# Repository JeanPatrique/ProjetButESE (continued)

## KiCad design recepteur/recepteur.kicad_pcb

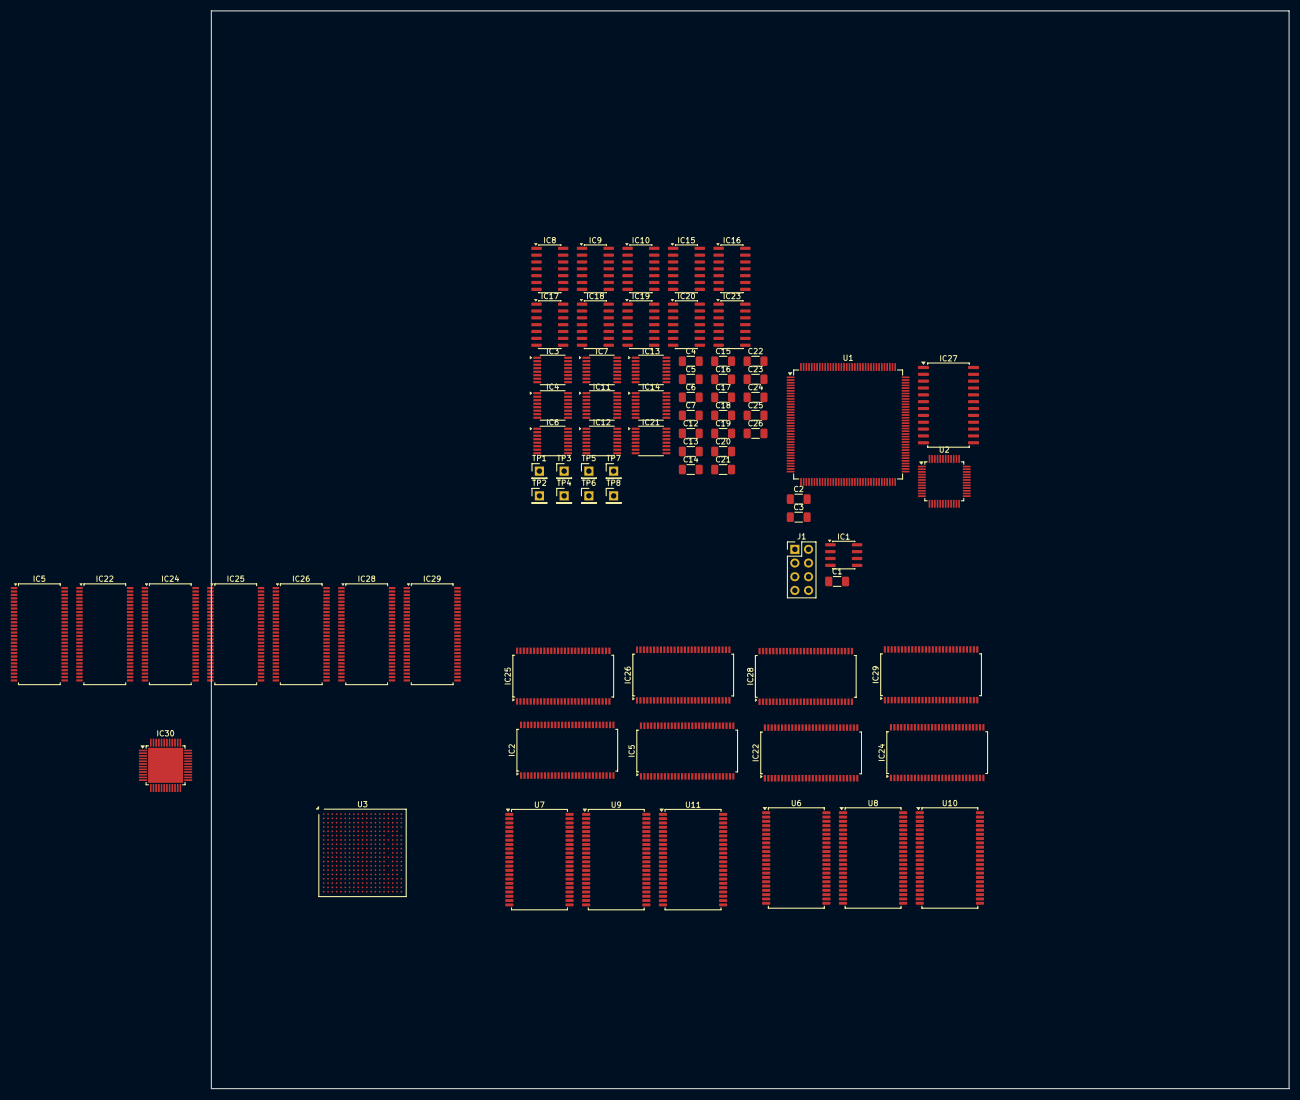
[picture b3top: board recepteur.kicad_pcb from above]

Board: 2 copper layers, 200.0 x 200.0 mm, 77 parts (0 on the bottom side), 311 nets.

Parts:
C1, C2, C3: C; C_1206_3216Metric_Pad1.33x1.80mm_HandSolder
C4, C5, C6, C7, C12, C13, C14, C15, C16, C17, C18, C19, C20, C21, C22, C23, C24, C25, C26: 100nF; C_1206_3216Metric_Pad1.33x1.80mm_HandSolder
IC1: 551MLF; SOIC-8_3.9x4.9mm_P1.27mm
IC2, IC5, IC5#2, IC22, IC22#2, IC24, IC24#2, IC25, IC25#2, IC26, IC26#2, IC28, IC28#2, IC29, IC29#2: SN74CBTD16211DLR; SSOP-56_7.5x18.5mm_P0.635mm
IC3, IC4, IC6, IC7: SN74LV4040APWR; TSSOP-16_4.4x5mm_P0.65mm
IC8, IC9, IC10, IC15, IC16, IC17, IC18, IC19, IC20, IC23: SN74F21DRE4; SOIC-14_3.9x8.7mm_P1.27mm
IC11, IC12, IC13, IC14, IC21: 74VHC112; TSSOP-16_4.4x5mm_P0.65mm
IC27: SN74LVCC4245A; SOIC-24W_7.5x15.4mm_P1.27mm
IC30: THS8135PHP; Texas_PHP0048E_HTQFP-48-1EP_7x7mm_P0.5mm_EP6.5x6.5mm_Mask3.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
J1: Conn_02x04_Counter_Clockwise; PinHeader_2x04_P2.54mm_Vertical
TP1, TP2, TP3, TP4, TP5, TP6, TP7, TP8: TestPoint; PinHeader_1x01_P2.54mm_Vertical
U1: STM32H733ZGTx; LQFP-144_20x20mm_P0.5mm
U2: STM32H523CETx; LQFP-48_7x7mm_P0.5mm
U3: STM32MP151DABx; ST_LFBGA-354_16x16mm_Layout19x19_P0.8mm
U6, U7, U8, U9, U10, U11: IS61C5128AL-10TLI; TSOP-II-44_10.16x18.41mm_P0.8mm

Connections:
/MCU/40MHZ_pixel_clock: IC1.1 (ICLK), IC27.3 (A0), IC27.21 (B0)
/MCU/RESET: IC27.5 (A2), IC27.19 (B2)
/MCU/pixelBufferMemoryAddress.A_{0}: IC24#2.54 (B_{1}_1), IC28#2.54 (B_{1}_1)
/MCU/pixelBufferMemoryAddress.A_{1}: IC24#2.53 (B_{1}_2), IC28#2.53 (B_{1}_2)
/MCU/pixelBufferMemoryAddress.A_{2}: IC24#2.52 (B_{1}_3), IC28#2.52 (B_{1}_3)
/MCU/pixelBufferMemoryAddress.A_{3}: IC24#2.51 (B_{1}_4), IC28#2.51 (B_{1}_4)
/MCU/pixelBufferMemoryAddress.A_{4}: IC24#2.50 (B_{1}_5), IC28#2.50 (B_{1}_5)
/MCU/pixelBufferMemoryAddress.A_{5}: IC24#2.48 (B_{1}_6), IC28#2.48 (B_{1}_6)
/MCU/pixelBufferMemoryAddress.A_{6}: IC24#2.47 (B_{1}_7), IC28#2.47 (B_{1}_7)
/MCU/pixelBufferMemoryAddress.A_{7}: IC24#2.46 (B_{1}_8), IC28#2.46 (B_{1}_8)
/MCU/pixelBufferMemoryAddress.A_{8}: IC24#2.45 (B_{1}_9), IC28#2.45 (B_{1}_9)
/MCU/pixelBufferMemoryAddress.A_{9}: IC24#2.44 (B_{1}_10), IC28#2.44 (B_{1}_10)
/MCU/pixelBufferMemoryAddress.A_{10}: IC24#2.43 (B_{1}_11), IC28#2.43 (B_{1}_11)
/MCU/pixelBufferMemoryAddress.A_{11}: IC24#2.42 (B_{1}_12), IC28#2.42 (B_{1}_12)
/MCU/pixelBufferMemoryAddress.A_{12}: IC24#2.41 (B_{2}_1), IC28#2.41 (B_{2}_1)
/MCU/pixelBufferMemoryAddress.A_{13}: IC24#2.40 (B_{2}_2), IC28#2.40 (B_{2}_2)
/MCU/pixelBufferMemoryAddress.A_{14}: IC24#2.39 (B_{2}_3), IC28#2.39 (B_{2}_3)
/MCU/pixelBufferMemoryAddress.A_{15}: IC24#2.37 (B_{2}_4), IC28#2.37 (B_{2}_4)
/MCU/pixelBufferMemoryAddress.A_{16}: IC24#2.36 (B_{2}_5), IC28#2.36 (B_{2}_5)
/MCU/pixelBufferMemoryAddress.A_{17}: IC24#2.35 (B_{2}_6), IC28#2.35 (B_{2}_6)
/MCU/pixelBufferMemoryAddress.A_{18}: IC24#2.34 (B_{2}_7), IC28#2.34 (B_{2}_7)
/MCU/pixelBuffer~WE: IC5.33 (B_{2}_8), IC24.33 (B_{2}_8), IC24#2.33 (B_{2}_8), IC28#2.33 (B_{2}_8)
/MCU/videoBufferSwapRequest_5V: IC19.8 (&), IC23.4 (C), IC23.5 (D), TP3.1
/MCU/~MCU_ACK_bufferSwap: IC23.1 (A), IC23.2 (B), IC27.10 (A7), IC27.14 (B7)
/Memory_bank_{0}/address.A_{0}: IC22.2 (A_{1}_1), IC24#2.2 (A_{1}_1)
/Memory_bank_{0}/address.A_{1}: IC22.3 (A_{1}_2), IC24#2.3 (A_{1}_2)
/Memory_bank_{0}/address.A_{2}: IC22.4 (A_{1}_3), IC24#2.4 (A_{1}_3)
/Memory_bank_{0}/address.A_{3}: IC22.5 (A_{1}_4), IC24#2.5 (A_{1}_4)
/Memory_bank_{0}/address.A_{4}: IC22.6 (A_{1}_5), IC24#2.6 (A_{1}_5)
/Memory_bank_{0}/address.A_{5}: IC22.7 (A_{1}_6), IC24#2.7 (A_{1}_6)
/Memory_bank_{0}/address.A_{6}: IC22.9 (A_{1}_7), IC24#2.9 (A_{1}_7)
/Memory_bank_{0}/address.A_{7}: IC22.10 (A_{1}_8), IC24#2.10 (A_{1}_8)
/Memory_bank_{0}/address.A_{8}: IC22.11 (A_{1}_9), IC24#2.11 (A_{1}_9)
/Memory_bank_{0}/address.A_{9}: IC22.12 (A_{1}_10), IC24#2.12 (A_{1}_10)
/Memory_bank_{0}/address.A_{10}: IC22.13 (A_{1}_11), IC24#2.13 (A_{1}_11)
/Memory_bank_{0}/address.A_{11}: IC22.14 (A_{1}_12), IC24#2.14 (A_{1}_12)
/Memory_bank_{0}/address.A_{12}: IC22.15 (A_{2}_1), IC24#2.15 (A_{2}_1)
/Memory_bank_{0}/address.A_{13}: IC22.16 (A_{2}_2), IC24#2.16 (A_{2}_2)
/Memory_bank_{0}/address.A_{14}: IC22.18 (A_{2}_3), IC24#2.18 (A_{2}_3)
/Memory_bank_{0}/address.A_{15}: IC22.20 (A_{2}_4), IC24#2.20 (A_{2}_4)
/Memory_bank_{0}/address.A_{16}: IC22.21 (A_{2}_5), IC24#2.21 (A_{2}_5)
/Memory_bank_{0}/address.A_{17}: IC22.22 (A_{2}_6), IC24#2.22 (A_{2}_6)
/Memory_bank_{0}/address.A_{18}: IC22.23 (A_{2}_7), IC24#2.23 (A_{2}_7)
/Memory_bank_{0}/data.D_{0}: IC2.2 (A_{1}_1), IC5#2.2 (A_{1}_1), U6.9 (I/O0)
/Memory_bank_{0}/data.D_{1}: IC2.3 (A_{1}_2), IC5#2.3 (A_{1}_2), U6.10 (I/O1)
/Memory_bank_{0}/data.D_{2}: IC2.4 (A_{1}_3), IC5#2.4 (A_{1}_3), U6.13 (I/O2)
/Memory_bank_{0}/data.D_{3}: IC2.5 (A_{1}_4), IC5#2.5 (A_{1}_4), U6.14 (I/O3)
/Memory_bank_{0}/data.D_{4}: IC2.6 (A_{1}_5), IC5#2.6 (A_{1}_5), U6.31 (I/O4)
/Memory_bank_{0}/data.D_{5}: IC2.7 (A_{1}_6), IC5#2.7 (A_{1}_6), U6.32 (I/O5)
/Memory_bank_{0}/data.D_{6}: IC2.9 (A_{1}_7), IC5#2.9 (A_{1}_7), U6.35 (I/O6)
/Memory_bank_{0}/data.D_{7}: IC2.10 (A_{1}_8), IC5#2.10 (A_{1}_8), U6.36 (I/O7)
/Memory_bank_{0}/data.D_{8}: IC2.11 (A_{1}_9), IC5#2.11 (A_{1}_9), U8.9 (I/O0)
/Memory_bank_{0}/data.D_{9}: IC2.12 (A_{1}_10), IC5#2.12 (A_{1}_10), U8.10 (I/O1)
/Memory_bank_{0}/data.D_{10}: IC2.13 (A_{1}_11), IC5#2.13 (A_{1}_11), U8.13 (I/O2)
/Memory_bank_{0}/data.D_{11}: IC2.14 (A_{1}_12), IC5#2.14 (A_{1}_12), U8.14 (I/O3)
/Memory_bank_{0}/data.D_{12}: IC2.15 (A_{2}_1), IC5#2.15 (A_{2}_1), U8.31 (I/O4)
/Memory_bank_{0}/data.D_{13}: IC2.16 (A_{2}_2), IC5#2.16 (A_{2}_2), U8.32 (I/O5)
/Memory_bank_{0}/data.D_{14}: IC2.18 (A_{2}_3), IC5#2.18 (A_{2}_3), U8.35 (I/O6)
/Memory_bank_{0}/data.D_{15}: IC2.20 (A_{2}_4), IC5#2.20 (A_{2}_4), U8.36 (I/O7)
/Memory_bank_{0}/data.D_{16}: IC2.21 (A_{2}_5), IC5#2.21 (A_{2}_5), U10.9 (I/O0)
/Memory_bank_{0}/data.D_{17}: IC2.22 (A_{2}_6), IC5#2.22 (A_{2}_6), U10.10 (I/O1)
/Memory_bank_{0}/data.D_{18}: IC2.23 (A_{2}_7), IC5#2.23 (A_{2}_7), U10.13 (I/O2)
/Memory_bank_{0}/data.D_{19}: IC2.24 (A_{2}_8), IC5#2.24 (A_{2}_8), U10.14 (I/O3)
/Memory_bank_{0}/data.D_{20}: IC2.25 (A_{2}_9), IC5#2.25 (A_{2}_9), U10.31 (I/O4)
/Memory_bank_{0}/data.D_{21}: IC2.26 (A_{2}_10), IC5#2.26 (A_{2}_10), U10.32 (I/O5)
/Memory_bank_{0}/data.D_{22}: IC2.27 (A_{2}_11), IC5#2.27 (A_{2}_11), U10.35 (I/O6)
/Memory_bank_{0}/data.D_{23}: IC2.28 (A_{2}_12), IC5#2.28 (A_{2}_12), U10.36 (I/O7)
/Memory_bank_{0}/pixelMemoryAddress.A_{0}: U6.3 (A0), U8.3 (A0), U10.3 (A0)
/Memory_bank_{0}/pixelMemoryAddress.A_{1}: U6.4 (A1), U8.4 (A1), U10.4 (A1)
/Memory_bank_{0}/pixelMemoryAddress.A_{2}: U6.5 (A2), U8.5 (A2), U10.5 (A2)
/Memory_bank_{0}/pixelMemoryAddress.A_{3}: U6.6 (A3), U8.6 (A3), U10.6 (A3)
/Memory_bank_{0}/pixelMemoryAddress.A_{4}: U6.7 (A4), U8.7 (A4), U10.7 (A4)
/Memory_bank_{0}/pixelMemoryAddress.A_{5}: U6.16 (A5), U8.16 (A5), U10.16 (A5)
/Memory_bank_{0}/pixelMemoryAddress.A_{6}: U6.17 (A6), U8.17 (A6), U10.17 (A6)
/Memory_bank_{0}/pixelMemoryAddress.A_{7}: U6.18 (A7), U8.18 (A7), U10.18 (A7)
/Memory_bank_{0}/pixelMemoryAddress.A_{8}: U6.19 (A8), U8.19 (A8), U10.19 (A8)
/Memory_bank_{0}/pixelMemoryAddress.A_{9}: U6.20 (A9), U8.20 (A9), U10.20 (A9)
/Memory_bank_{0}/pixelMemoryAddress.A_{10}: U6.26 (A10), U8.26 (A10), U10.26 (A10)
/Memory_bank_{0}/pixelMemoryAddress.A_{11}: U6.27 (A11), U8.27 (A11), U10.27 (A11)
/Memory_bank_{0}/pixelMemoryAddress.A_{12}: U6.28 (A12), U8.28 (A12), U10.28 (A12)
/Memory_bank_{0}/pixelMemoryAddress.A_{13}: U6.29 (A13), U8.29 (A13), U10.29 (A13)
/Memory_bank_{0}/pixelMemoryAddress.A_{14}: U6.30 (A14), U8.30 (A14), U10.30 (A14)
/Memory_bank_{0}/pixelMemoryAddress.A_{15}: U6.38 (A15), U8.38 (A15), U10.38 (A15)
/Memory_bank_{0}/pixelMemoryAddress.A_{16}: U6.39 (A16), U8.39 (A16), U10.39 (A16)
/Memory_bank_{0}/pixelMemoryAddress.A_{17}: U6.40 (A17), U8.40 (A17), U10.40 (A17)
/Memory_bank_{0}/pixelMemoryAddress.A_{18}: U6.41 (A18), U8.41 (A18), U10.41 (A18)
/Memory_bank_{1}/address.A_{0}: IC28#2.2 (A_{1}_1), IC29#2.2 (A_{1}_1)
/Memory_bank_{1}/address.A_{1}: IC28#2.3 (A_{1}_2), IC29#2.3 (A_{1}_2)
/Memory_bank_{1}/address.A_{2}: IC28#2.4 (A_{1}_3), IC29#2.4 (A_{1}_3)
/Memory_bank_{1}/address.A_{3}: IC28#2.5 (A_{1}_4), IC29#2.5 (A_{1}_4)
/Memory_bank_{1}/address.A_{4}: IC28#2.6 (A_{1}_5), IC29#2.6 (A_{1}_5)
/Memory_bank_{1}/address.A_{5}: IC28#2.7 (A_{1}_6), IC29#2.7 (A_{1}_6)
/Memory_bank_{1}/address.A_{6}: IC28#2.9 (A_{1}_7), IC29#2.9 (A_{1}_7)
/Memory_bank_{1}/address.A_{7}: IC28#2.10 (A_{1}_8), IC29#2.10 (A_{1}_8)
/Memory_bank_{1}/address.A_{8}: IC28#2.11 (A_{1}_9), IC29#2.11 (A_{1}_9)
/Memory_bank_{1}/address.A_{9}: IC28#2.12 (A_{1}_10), IC29#2.12 (A_{1}_10)
/Memory_bank_{1}/address.A_{10}: IC28#2.13 (A_{1}_11), IC29#2.13 (A_{1}_11)
/Memory_bank_{1}/address.A_{11}: IC28#2.14 (A_{1}_12), IC29#2.14 (A_{1}_12)
/Memory_bank_{1}/address.A_{12}: IC28#2.15 (A_{2}_1), IC29#2.15 (A_{2}_1)
/Memory_bank_{1}/address.A_{13}: IC28#2.16 (A_{2}_2), IC29#2.16 (A_{2}_2)
/Memory_bank_{1}/address.A_{14}: IC28#2.18 (A_{2}_3), IC29#2.18 (A_{2}_3)
/Memory_bank_{1}/address.A_{15}: IC28#2.20 (A_{2}_4), IC29#2.20 (A_{2}_4)
/Memory_bank_{1}/address.A_{16}: IC28#2.21 (A_{2}_5), IC29#2.21 (A_{2}_5)
/Memory_bank_{1}/address.A_{17}: IC28#2.22 (A_{2}_6), IC29#2.22 (A_{2}_6)
/Memory_bank_{1}/address.A_{18}: IC28#2.23 (A_{2}_7), IC29#2.23 (A_{2}_7)
/Memory_bank_{1}/data.D_{0}: IC25#2.2 (A_{1}_1), IC26.2 (A_{1}_1), U7.9 (I/O0)
/Memory_bank_{1}/data.D_{1}: IC25#2.3 (A_{1}_2), IC26.3 (A_{1}_2), U7.10 (I/O1)
/Memory_bank_{1}/data.D_{2}: IC25#2.4 (A_{1}_3), IC26.4 (A_{1}_3), U7.13 (I/O2)
/Memory_bank_{1}/data.D_{3}: IC25#2.5 (A_{1}_4), IC26.5 (A_{1}_4), U7.14 (I/O3)
/Memory_bank_{1}/data.D_{4}: IC25#2.6 (A_{1}_5), IC26.6 (A_{1}_5), U7.31 (I/O4)
/Memory_bank_{1}/data.D_{5}: IC25#2.7 (A_{1}_6), IC26.7 (A_{1}_6), U7.32 (I/O5)
/Memory_bank_{1}/data.D_{6}: IC25#2.9 (A_{1}_7), IC26.9 (A_{1}_7), U7.35 (I/O6)
/Memory_bank_{1}/data.D_{7}: IC25#2.10 (A_{1}_8), IC26.10 (A_{1}_8), U7.36 (I/O7)
/Memory_bank_{1}/data.D_{8}: IC25#2.11 (A_{1}_9), IC26.11 (A_{1}_9), U9.9 (I/O0)
/Memory_bank_{1}/data.D_{9}: IC25#2.12 (A_{1}_10), IC26.12 (A_{1}_10), U9.10 (I/O1)
/Memory_bank_{1}/data.D_{10}: IC25#2.13 (A_{1}_11), IC26.13 (A_{1}_11), U9.13 (I/O2)
/Memory_bank_{1}/data.D_{11}: IC25#2.14 (A_{1}_12), IC26.14 (A_{1}_12), U9.14 (I/O3)
/Memory_bank_{1}/data.D_{12}: IC25#2.15 (A_{2}_1), IC26.15 (A_{2}_1), U9.31 (I/O4)
/Memory_bank_{1}/data.D_{13}: IC25#2.16 (A_{2}_2), IC26.16 (A_{2}_2), U9.32 (I/O5)
/Memory_bank_{1}/data.D_{14}: IC25#2.18 (A_{2}_3), IC26.18 (A_{2}_3), U9.35 (I/O6)
/Memory_bank_{1}/data.D_{15}: IC25#2.20 (A_{2}_4), IC26.20 (A_{2}_4), U9.36 (I/O7)
/Memory_bank_{1}/data.D_{16}: IC25#2.21 (A_{2}_5), IC26.21 (A_{2}_5), U11.9 (I/O0)
/Memory_bank_{1}/data.D_{17}: IC25#2.22 (A_{2}_6), IC26.22 (A_{2}_6), U11.10 (I/O1)
/Memory_bank_{1}/data.D_{18}: IC25#2.23 (A_{2}_7), IC26.23 (A_{2}_7), U11.13 (I/O2)
/Memory_bank_{1}/data.D_{19}: IC25#2.24 (A_{2}_8), IC26.24 (A_{2}_8), U11.14 (I/O3)
/Memory_bank_{1}/data.D_{20}: IC25#2.25 (A_{2}_9), IC26.25 (A_{2}_9), U11.31 (I/O4)
/Memory_bank_{1}/data.D_{21}: IC25#2.26 (A_{2}_10), IC26.26 (A_{2}_10), U11.32 (I/O5)
/Memory_bank_{1}/data.D_{22}: IC25#2.27 (A_{2}_11), IC26.27 (A_{2}_11), U11.35 (I/O6)
/Memory_bank_{1}/data.D_{23}: IC25#2.28 (A_{2}_12), IC26.28 (A_{2}_12), U11.36 (I/O7)
/Memory_bank_{1}/pixelMemoryAddress.A_{0}: U7.3 (A0), U9.3 (A0), U11.3 (A0)
/Memory_bank_{1}/pixelMemoryAddress.A_{1}: U7.4 (A1), U9.4 (A1), U11.4 (A1)
/Memory_bank_{1}/pixelMemoryAddress.A_{2}: U7.5 (A2), U9.5 (A2), U11.5 (A2)
/Memory_bank_{1}/pixelMemoryAddress.A_{3}: U7.6 (A3), U9.6 (A3), U11.6 (A3)
/Memory_bank_{1}/pixelMemoryAddress.A_{4}: U7.7 (A4), U9.7 (A4), U11.7 (A4)
/Memory_bank_{1}/pixelMemoryAddress.A_{5}: U7.16 (A5), U9.16 (A5), U11.16 (A5)
/Memory_bank_{1}/pixelMemoryAddress.A_{6}: U7.17 (A6), U9.17 (A6), U11.17 (A6)
/Memory_bank_{1}/pixelMemoryAddress.A_{7}: U7.18 (A7), U9.18 (A7), U11.18 (A7)
/Memory_bank_{1}/pixelMemoryAddress.A_{8}: U7.19 (A8), U9.19 (A8), U11.19 (A8)
/Memory_bank_{1}/pixelMemoryAddress.A_{9}: U7.20 (A9), U9.20 (A9), U11.20 (A9)
/Memory_bank_{1}/pixelMemoryAddress.A_{10}: U7.26 (A10), U9.26 (A10), U11.26 (A10)
/Memory_bank_{1}/pixelMemoryAddress.A_{11}: U7.27 (A11), U9.27 (A11), U11.27 (A11)
/Memory_bank_{1}/pixelMemoryAddress.A_{12}: U7.28 (A12), U9.28 (A12), U11.28 (A12)
/Memory_bank_{1}/pixelMemoryAddress.A_{13}: U7.29 (A13), U9.29 (A13), U11.29 (A13)
/Memory_bank_{1}/pixelMemoryAddress.A_{14}: U7.30 (A14), U9.30 (A14), U11.30 (A14)
/Memory_bank_{1}/pixelMemoryAddress.A_{15}: U7.38 (A15), U9.38 (A15), U11.38 (A15)
/Memory_bank_{1}/pixelMemoryAddress.A_{16}: U7.39 (A16), U9.39 (A16), U11.39 (A16)
/Memory_bank_{1}/pixelMemoryAddress.A_{17}: U7.40 (A17), U9.40 (A17), U11.40 (A17)
/Memory_bank_{1}/pixelMemoryAddress.A_{18}: U7.41 (A18), U9.41 (A18), U11.41 (A18)
/VGA_controller/Buffer_pixelAddress.A_{0}: IC5.2 (A_{1}_1), IC5.54 (B_{1}_1), IC22.54 (B_{1}_1), IC24.2 (A_{1}_1), IC24.54 (B_{1}_1), IC26#2.2 (A_{1}_1), IC26#2.54 (B_{1}_1), IC29.2 (A_{1}_1), IC29.54 (B_{1}_1), IC29#2.54 (B_{1}_1)
/VGA_controller/Buffer_pixelAddress.A_{1}: IC5.3 (A_{1}_2), IC5.53 (B_{1}_2), IC22.53 (B_{1}_2), IC24.3 (A_{1}_2), IC24.53 (B_{1}_2), IC26#2.3 (A_{1}_2), IC26#2.53 (B_{1}_2), IC29.3 (A_{1}_2), IC29.53 (B_{1}_2), IC29#2.53 (B_{1}_2)
/VGA_controller/Buffer_pixelAddress.A_{2}: IC5.4 (A_{1}_3), IC5.52 (B_{1}_3), IC22.52 (B_{1}_3), IC24.4 (A_{1}_3), IC24.52 (B_{1}_3), IC26#2.4 (A_{1}_3), IC26#2.52 (B_{1}_3), IC29.4 (A_{1}_3), IC29.52 (B_{1}_3), IC29#2.52 (B_{1}_3)
/VGA_controller/Buffer_pixelAddress.A_{3}: IC5.5 (A_{1}_4), IC5.51 (B_{1}_4), IC22.51 (B_{1}_4), IC24.5 (A_{1}_4), IC24.51 (B_{1}_4), IC26#2.5 (A_{1}_4), IC26#2.51 (B_{1}_4), IC29.5 (A_{1}_4), IC29.51 (B_{1}_4), IC29#2.51 (B_{1}_4)
/VGA_controller/Buffer_pixelAddress.A_{4}: IC5.6 (A_{1}_5), IC5.50 (B_{1}_5), IC22.50 (B_{1}_5), IC24.6 (A_{1}_5), IC24.50 (B_{1}_5), IC26#2.6 (A_{1}_5), IC26#2.50 (B_{1}_5), IC29.6 (A_{1}_5), IC29.50 (B_{1}_5), IC29#2.50 (B_{1}_5)
/VGA_controller/Buffer_pixelAddress.A_{5}: IC5.7 (A_{1}_6), IC5.48 (B_{1}_6), IC22.48 (B_{1}_6), IC24.7 (A_{1}_6), IC24.48 (B_{1}_6), IC26#2.7 (A_{1}_6), IC26#2.48 (B_{1}_6), IC29.7 (A_{1}_6), IC29.48 (B_{1}_6), IC29#2.48 (B_{1}_6)
/VGA_controller/Buffer_pixelAddress.A_{6}: IC5.9 (A_{1}_7), IC5.47 (B_{1}_7), IC22.47 (B_{1}_7), IC24.9 (A_{1}_7), IC24.47 (B_{1}_7), IC26#2.9 (A_{1}_7), IC26#2.47 (B_{1}_7), IC29.9 (A_{1}_7), IC29.47 (B_{1}_7), IC29#2.47 (B_{1}_7)
/VGA_controller/Buffer_pixelAddress.A_{7}: IC5.10 (A_{1}_8), IC5.46 (B_{1}_8), IC22.46 (B_{1}_8), IC24.10 (A_{1}_8), IC24.46 (B_{1}_8), IC26#2.10 (A_{1}_8), IC26#2.46 (B_{1}_8), IC29.10 (A_{1}_8), IC29.46 (B_{1}_8), IC29#2.46 (B_{1}_8)
/VGA_controller/Buffer_pixelAddress.A_{8}: IC5.11 (A_{1}_9), IC5.45 (B_{1}_9), IC22.45 (B_{1}_9), IC24.11 (A_{1}_9), IC24.45 (B_{1}_9), IC26#2.11 (A_{1}_9), IC26#2.45 (B_{1}_9), IC29.11 (A_{1}_9), IC29.45 (B_{1}_9), IC29#2.45 (B_{1}_9)
/VGA_controller/Buffer_pixelAddress.A_{9}: IC5.12 (A_{1}_10), IC5.44 (B_{1}_10), IC22.44 (B_{1}_10), IC24.12 (A_{1}_10), IC24.44 (B_{1}_10), IC26#2.12 (A_{1}_10), IC26#2.44 (B_{1}_10), IC29.12 (A_{1}_10), IC29.44 (B_{1}_10), IC29#2.44 (B_{1}_10)
/VGA_controller/Buffer_pixelAddress.A_{10}: IC5.13 (A_{1}_11), IC5.43 (B_{1}_11), IC22.43 (B_{1}_11), IC24.13 (A_{1}_11), IC24.43 (B_{1}_11), IC26#2.13 (A_{1}_11), IC26#2.43 (B_{1}_11), IC29.13 (A_{1}_11), IC29.43 (B_{1}_11), IC29#2.43 (B_{1}_11)
/VGA_controller/Buffer_pixelAddress.A_{11}: IC5.14 (A_{1}_12), IC5.42 (B_{1}_12), IC22.42 (B_{1}_12), IC24.14 (A_{1}_12), IC24.42 (B_{1}_12), IC26#2.14 (A_{1}_12), IC26#2.42 (B_{1}_12), IC29.14 (A_{1}_12), IC29.42 (B_{1}_12), IC29#2.42 (B_{1}_12)
/VGA_controller/Buffer_pixelAddress.A_{12}: IC5.15 (A_{2}_1), IC5.41 (B_{2}_1), IC22.41 (B_{2}_1), IC24.15 (A_{2}_1), IC24.41 (B_{2}_1), IC26#2.15 (A_{2}_1), IC26#2.41 (B_{2}_1), IC29.15 (A_{2}_1), IC29.41 (B_{2}_1), IC29#2.41 (B_{2}_1)
/VGA_controller/Buffer_pixelAddress.A_{13}: IC5.16 (A_{2}_2), IC5.40 (B_{2}_2), IC22.40 (B_{2}_2), IC24.16 (A_{2}_2), IC24.40 (B_{2}_2), IC26#2.16 (A_{2}_2), IC26#2.40 (B_{2}_2), IC29.16 (A_{2}_2), IC29.40 (B_{2}_2), IC29#2.40 (B_{2}_2)
/VGA_controller/Buffer_pixelAddress.A_{14}: IC5.18 (A_{2}_3), IC5.39 (B_{2}_3), IC22.39 (B_{2}_3), IC24.18 (A_{2}_3), IC24.39 (B_{2}_3), IC26#2.18 (A_{2}_3), IC26#2.39 (B_{2}_3), IC29.18 (A_{2}_3), IC29.39 (B_{2}_3), IC29#2.39 (B_{2}_3)
/VGA_controller/Buffer_pixelAddress.A_{15}: IC5.20 (A_{2}_4), IC5.37 (B_{2}_4), IC22.37 (B_{2}_4), IC24.20 (A_{2}_4), IC24.37 (B_{2}_4), IC26#2.20 (A_{2}_4), IC26#2.37 (B_{2}_4), IC29.20 (A_{2}_4), IC29.37 (B_{2}_4), IC29#2.37 (B_{2}_4)
/VGA_controller/Buffer_pixelAddress.A_{16}: IC5.21 (A_{2}_5), IC5.36 (B_{2}_5), IC22.36 (B_{2}_5), IC24.21 (A_{2}_5), IC24.36 (B_{2}_5), IC26#2.21 (A_{2}_5), IC26#2.36 (B_{2}_5), IC29.21 (A_{2}_5), IC29.36 (B_{2}_5), IC29#2.36 (B_{2}_5)
/VGA_controller/Buffer_pixelAddress.A_{17}: IC5.22 (A_{2}_6), IC5.35 (B_{2}_6), IC22.35 (B_{2}_6), IC24.22 (A_{2}_6), IC24.35 (B_{2}_6), IC26#2.22 (A_{2}_6), IC26#2.35 (B_{2}_6), IC29.22 (A_{2}_6), IC29.35 (B_{2}_6), IC29#2.35 (B_{2}_6)
/VGA_controller/Buffer_pixelAddress.A_{18}: IC5.23 (A_{2}_7), IC5.34 (B_{2}_7), IC22.34 (B_{2}_7), IC24.23 (A_{2}_7), IC24.34 (B_{2}_7), IC26#2.23 (A_{2}_7), IC26#2.34 (B_{2}_7), IC29.23 (A_{2}_7), IC29.34 (B_{2}_7), IC29#2.34 (B_{2}_7)
/VGA_controller/Buffer_pixelData.A_{0}: IC22#2.2 (A_{1}_1), IC22#2.54 (B_{1}_1), IC25.2 (A_{1}_1), IC25.54 (B_{1}_1), IC28.2 (A_{1}_1), IC28.54 (B_{1}_1)
/VGA_controller/Buffer_pixelData.A_{1}: IC22#2.3 (A_{1}_2), IC22#2.53 (B_{1}_2), IC25.3 (A_{1}_2), IC25.53 (B_{1}_2), IC28.3 (A_{1}_2), IC28.53 (B_{1}_2)
/VGA_controller/Buffer_pixelData.A_{2}: IC22#2.4 (A_{1}_3), IC22#2.52 (B_{1}_3), IC25.4 (A_{1}_3), IC25.52 (B_{1}_3), IC28.4 (A_{1}_3), IC28.52 (B_{1}_3)
/VGA_controller/Buffer_pixelData.A_{3}: IC22#2.5 (A_{1}_4), IC22#2.51 (B_{1}_4), IC25.5 (A_{1}_4), IC25.51 (B_{1}_4), IC28.5 (A_{1}_4), IC28.51 (B_{1}_4)
/VGA_controller/Buffer_pixelData.A_{4}: IC22#2.6 (A_{1}_5), IC22#2.50 (B_{1}_5), IC25.6 (A_{1}_5), IC25.50 (B_{1}_5), IC28.6 (A_{1}_5), IC28.50 (B_{1}_5)
/VGA_controller/Buffer_pixelData.A_{5}: IC22#2.7 (A_{1}_6), IC22#2.48 (B_{1}_6), IC25.7 (A_{1}_6), IC25.48 (B_{1}_6), IC28.7 (A_{1}_6), IC28.48 (B_{1}_6)
/VGA_controller/Buffer_pixelData.A_{6}: IC22#2.9 (A_{1}_7), IC22#2.47 (B_{1}_7), IC25.9 (A_{1}_7), IC25.47 (B_{1}_7), IC28.9 (A_{1}_7), IC28.47 (B_{1}_7)
/VGA_controller/Buffer_pixelData.A_{7}: IC22#2.10 (A_{1}_8), IC22#2.46 (B_{1}_8), IC25.10 (A_{1}_8), IC25.46 (B_{1}_8), IC28.10 (A_{1}_8), IC28.46 (B_{1}_8)
/VGA_controller/Buffer_pixelData.A_{8}: IC22#2.11 (A_{1}_9), IC22#2.45 (B_{1}_9), IC25.11 (A_{1}_9), IC25.45 (B_{1}_9), IC28.11 (A_{1}_9), IC28.45 (B_{1}_9)
/VGA_controller/Buffer_pixelData.A_{9}: IC22#2.12 (A_{1}_10), IC22#2.44 (B_{1}_10), IC25.12 (A_{1}_10), IC25.44 (B_{1}_10), IC28.12 (A_{1}_10), IC28.44 (B_{1}_10)
/VGA_controller/Buffer_pixelData.A_{10}: IC22#2.13 (A_{1}_11), IC22#2.43 (B_{1}_11), IC25.13 (A_{1}_11), IC25.43 (B_{1}_11), IC28.13 (A_{1}_11), IC28.43 (B_{1}_11)
/VGA_controller/Buffer_pixelData.A_{11}: IC22#2.14 (A_{1}_12), IC22#2.42 (B_{1}_12), IC25.14 (A_{1}_12), IC25.42 (B_{1}_12), IC28.14 (A_{1}_12), IC28.42 (B_{1}_12)
/VGA_controller/Buffer_pixelData.A_{12}: IC22#2.15 (A_{2}_1), IC22#2.41 (B_{2}_1), IC25.15 (A_{2}_1), IC25.41 (B_{2}_1), IC28.15 (A_{2}_1), IC28.41 (B_{2}_1)
/VGA_controller/Buffer_pixelData.A_{13}: IC22#2.16 (A_{2}_2), IC22#2.40 (B_{2}_2), IC25.16 (A_{2}_2), IC25.40 (B_{2}_2), IC28.16 (A_{2}_2), IC28.40 (B_{2}_2)
/VGA_controller/Buffer_pixelData.A_{14}: IC22#2.18 (A_{2}_3), IC22#2.39 (B_{2}_3), IC25.18 (A_{2}_3), IC25.39 (B_{2}_3), IC28.18 (A_{2}_3), IC28.39 (B_{2}_3)
/VGA_controller/Buffer_pixelData.A_{15}: IC22#2.20 (A_{2}_4), IC22#2.37 (B_{2}_4), IC25.20 (A_{2}_4), IC25.37 (B_{2}_4), IC28.20 (A_{2}_4), IC28.37 (B_{2}_4)
/VGA_controller/Buffer_pixelData.A_{16}: IC22#2.21 (A_{2}_5), IC22#2.36 (B_{2}_5), IC25.21 (A_{2}_5), IC25.36 (B_{2}_5), IC28.21 (A_{2}_5), IC28.36 (B_{2}_5)
/VGA_controller/Buffer_pixelData.A_{17}: IC22#2.22 (A_{2}_6), IC22#2.35 (B_{2}_6), IC25.22 (A_{2}_6), IC25.35 (B_{2}_6), IC28.22 (A_{2}_6), IC28.35 (B_{2}_6)
/VGA_controller/Buffer_pixelData.A_{18}: IC22#2.23 (A_{2}_7), IC22#2.34 (B_{2}_7), IC25.23 (A_{2}_7), IC25.34 (B_{2}_7), IC28.23 (A_{2}_7), IC28.34 (B_{2}_7)
/VGA_controller/Buffer_pixelData.A_{19}: IC22#2.24 (A_{2}_8), IC22#2.33 (B_{2}_8), IC25.24 (A_{2}_8), IC25.33 (B_{2}_8), IC28.24 (A_{2}_8), IC28.33 (B_{2}_8)
/VGA_controller/Buffer_pixelData.A_{20}: IC22#2.25 (A_{2}_9), IC22#2.32 (B_{2}_9), IC25.25 (A_{2}_9), IC25.32 (B_{2}_9), IC28.25 (A_{2}_9), IC28.32 (B_{2}_9)
/VGA_controller/Buffer_pixelData.A_{21}: IC22#2.26 (A_{2}_10), IC22#2.31 (B_{2}_10), IC25.26 (A_{2}_10), IC25.31 (B_{2}_10), IC28.26 (A_{2}_10), IC28.31 (B_{2}_10)
/VGA_controller/Buffer_pixelData.A_{22}: IC22#2.27 (A_{2}_11), IC22#2.30 (B_{2}_11), IC25.27 (A_{2}_11), IC25.30 (B_{2}_11), IC28.27 (A_{2}_11), IC28.30 (B_{2}_11)
/VGA_controller/Buffer_pixelData.A_{23}: IC22#2.28 (A_{2}_12), IC22#2.29 (B_{2}_12), IC25.28 (A_{2}_12), IC25.29 (B_{2}_12), IC28.28 (A_{2}_12), IC28.29 (B_{2}_12)
/VGA_controller/Buffer_pixelData.D_{0}: IC2.54 (B_{1}_1), IC26.54 (B_{1}_1)
/VGA_controller/Buffer_pixelData.D_{1}: IC2.53 (B_{1}_2), IC26.53 (B_{1}_2)
/VGA_controller/Buffer_pixelData.D_{2}: IC2.52 (B_{1}_3), IC26.52 (B_{1}_3)
/VGA_controller/Buffer_pixelData.D_{3}: IC2.51 (B_{1}_4), IC26.51 (B_{1}_4)
/VGA_controller/Buffer_pixelData.D_{4}: IC2.50 (B_{1}_5), IC26.50 (B_{1}_5)
/VGA_controller/Buffer_pixelData.D_{5}: IC2.48 (B_{1}_6), IC26.48 (B_{1}_6)
/VGA_controller/Buffer_pixelData.D_{6}: IC2.47 (B_{1}_7), IC26.47 (B_{1}_7)
/VGA_controller/Buffer_pixelData.D_{7}: IC2.46 (B_{1}_8), IC26.46 (B_{1}_8)
/VGA_controller/Buffer_pixelData.D_{8}: IC2.45 (B_{1}_9), IC26.45 (B_{1}_9)
/VGA_controller/Buffer_pixelData.D_{9}: IC2.44 (B_{1}_10), IC26.44 (B_{1}_10)
/VGA_controller/Buffer_pixelData.D_{10}: IC2.43 (B_{1}_11), IC26.43 (B_{1}_11)
/VGA_controller/Buffer_pixelData.D_{11}: IC2.42 (B_{1}_12), IC26.42 (B_{1}_12)
/VGA_controller/Buffer_pixelData.D_{12}: IC2.41 (B_{2}_1), IC26.41 (B_{2}_1)
/VGA_controller/Buffer_pixelData.D_{13}: IC2.40 (B_{2}_2), IC26.40 (B_{2}_2)
/VGA_controller/Buffer_pixelData.D_{14}: IC2.39 (B_{2}_3), IC26.39 (B_{2}_3)
/VGA_controller/Buffer_pixelData.D_{15}: IC2.37 (B_{2}_4), IC26.37 (B_{2}_4)
/VGA_controller/Buffer_pixelData.D_{16}: IC2.36 (B_{2}_5), IC26.36 (B_{2}_5)
/VGA_controller/Buffer_pixelData.D_{17}: IC2.35 (B_{2}_6), IC26.35 (B_{2}_6)
/VGA_controller/Buffer_pixelData.D_{18}: IC2.34 (B_{2}_7), IC26.34 (B_{2}_7)
/VGA_controller/Buffer_pixelData.D_{19}: IC2.33 (B_{2}_8), IC26.33 (B_{2}_8)
/VGA_controller/Buffer_pixelData.D_{20}: IC2.32 (B_{2}_9), IC26.32 (B_{2}_9)
/VGA_controller/Buffer_pixelData.D_{21}: IC2.31 (B_{2}_10), IC26.31 (B_{2}_10)
/VGA_controller/Buffer_pixelData.D_{22}: IC2.30 (B_{2}_11), IC26.30 (B_{2}_11)
/VGA_controller/Buffer_pixelData.D_{23}: IC2.29 (B_{2}_12), IC26.29 (B_{2}_12)
/VGA_signals_timing_generator/10Mhz_VGA_clock: IC11.1 (~CLK), IC11.13 (~CLK), IC12.1 (~CLK), IC12.13 (~CLK), IC13.1 (~CLK), IC13.13 (~CLK), IC14.1 (~CLK), IC14.13 (~CLK)
/VGA_signals_timing_generator/40Mhz_VGA_clock: IC1.2 (Q1), IC8.2 (B)
/VGA_signals_timing_generator/H_CNTR_{3}: IC3.5 (Q_{3}), IC10.12 (C), IC10.13 (D), IC15.2 (B)
/VGA_signals_timing_generator/H_CNTR_{5}: IC3.2 (Q_{5}), IC10.2 (B), IC16.4 (C)
/VGA_signals_timing_generator/H_CNTR_{6}: IC3.4 (Q_{6}), IC15.4 (C)
/VGA_signals_timing_generator/H_CNTR_{7}: IC3.13 (Q_{7}), IC15.5 (D)
/VGA_signals_timing_generator/H_CNTR_{8}: IC3.12 (Q_{8}), IC10.4 (C)
/VGA_signals_timing_generator/H_CNTR_{9}: IC3.14 (Q_{9}), IC10.5 (D)
/VGA_signals_timing_generator/H_CNTR_{10}: IC3.15 (Q_{10}), IC16.5 (D)
/VGA_signals_timing_generator/H_FrontPorch: IC17.6 (&), TP7.1
/VGA_signals_timing_generator/H_SyncPulse: IC17.8 (&), TP6.1
/VGA_signals_timing_generator/H_backPorch: IC16.8 (&), TP5.1
/VGA_signals_timing_generator/H_reset: IC3.11 (CLR), IC4.10 (~CLK), IC11.2 (K), IC11.12 (K), IC12.2 (K), IC12.9 (Q), IC12.12 (K)
/VGA_signals_timing_generator/H_visible: IC8.4 (C), IC8.12 (C), IC11.6 (~Q), TP8.1
/VGA_signals_timing_generator/V_CNTR_{0}: IC4.9 (Q_{0}), IC18.5 (D), IC19.4 (C)
/VGA_signals_timing_generator/V_CNTR_{2}: IC4.6 (Q_{2}), IC19.5 (D), IC20.2 (B)
/VGA_signals_timing_generator/V_CNTR_{3}: IC4.5 (Q_{3}), IC9.9 (A)
/VGA_signals_timing_generator/V_CNTR_{4}: IC4.3 (Q_{4}), IC9.10 (B), IC20.4 (C)
/VGA_signals_timing_generator/V_CNTR_{5}: IC4.2 (Q_{5}), IC20.5 (D)
/VGA_signals_timing_generator/V_CNTR_{6}: IC4.4 (Q_{6}), IC9.12 (C)
/VGA_signals_timing_generator/V_CNTR_{9}: IC4.14 (Q_{9}), IC9.13 (D)
/VGA_signals_timing_generator/V_FrontPorch: IC18.8 (&), TP2.1
/VGA_signals_timing_generator/V_backPorch: IC7.11 (CLR), IC20.8 (&), TP4.1
/VGA_signals_timing_generator/V_reset: IC4.11 (CLR), IC13.2 (K), IC13.12 (K), IC14.2 (K), IC14.9 (Q), IC14.12 (K)
/VGA_signals_timing_generator/V_visible: IC8.5 (D), IC8.13 (D), IC13.6 (~Q), TP1.1
/VGA_signals_timing_generator/firstCounterOverflow: IC6.1 (Q_{11}), IC6.11 (CLR), IC8.10 (B)
/VGA_signals_timing_generator/~RESET: IC11.14 (~CLR), IC11.15 (~CLR), IC12.14 (~CLR), IC12.15 (~CLR), IC13.14 (~CLR), IC13.15 (~CLR), IC14.14 (~CLR), IC14.15 (~CLR), IC21.4 (~PRESET)
/Video_bus/Bank_0_~WE: IC22.24 (A_{2}_8), IC24#2.24 (A_{2}_8), U6.15 (~WE), U8.15 (~WE), U10.15 (~WE)
/Video_bus/Bank_1_~WE: IC28#2.24 (A_{2}_8), IC29#2.24 (A_{2}_8), U7.15 (~WE), U9.15 (~WE), U11.15 (~WE)
/Video_bus/F~B: IC5#2.55 (2~OE), IC5#2.56 (1~OE), IC21.5 (Q), IC24#2.55 (2~OE), IC24#2.56 (1~OE), IC26.55 (2~OE), IC26.56 (1~OE), IC29#2.55 (2~OE), IC29#2.56 (1~OE)
/Video_bus/MCU_pixelData.D_{0}: IC5#2.54 (B_{1}_1), IC25#2.54 (B_{1}_1)
/Video_bus/MCU_pixelData.D_{1}: IC5#2.53 (B_{1}_2), IC25#2.53 (B_{1}_2)
/Video_bus/MCU_pixelData.D_{2}: IC5#2.52 (B_{1}_3), IC25#2.52 (B_{1}_3)
/Video_bus/MCU_pixelData.D_{3}: IC5#2.51 (B_{1}_4), IC25#2.51 (B_{1}_4)
/Video_bus/MCU_pixelData.D_{4}: IC5#2.50 (B_{1}_5), IC25#2.50 (B_{1}_5)
/Video_bus/MCU_pixelData.D_{5}: IC5#2.48 (B_{1}_6), IC25#2.48 (B_{1}_6)
/Video_bus/MCU_pixelData.D_{6}: IC5#2.47 (B_{1}_7), IC25#2.47 (B_{1}_7)
/Video_bus/MCU_pixelData.D_{7}: IC5#2.46 (B_{1}_8), IC25#2.46 (B_{1}_8)
/Video_bus/MCU_pixelData.D_{8}: IC5#2.45 (B_{1}_9), IC25#2.45 (B_{1}_9)
/Video_bus/MCU_pixelData.D_{9}: IC5#2.44 (B_{1}_10), IC25#2.44 (B_{1}_10)
/Video_bus/MCU_pixelData.D_{10}: IC5#2.43 (B_{1}_11), IC25#2.43 (B_{1}_11)
/Video_bus/MCU_pixelData.D_{11}: IC5#2.42 (B_{1}_12), IC25#2.42 (B_{1}_12)
/Video_bus/MCU_pixelData.D_{12}: IC5#2.41 (B_{2}_1), IC25#2.41 (B_{2}_1)
/Video_bus/MCU_pixelData.D_{13}: IC5#2.40 (B_{2}_2), IC25#2.40 (B_{2}_2)
/Video_bus/MCU_pixelData.D_{14}: IC5#2.39 (B_{2}_3), IC25#2.39 (B_{2}_3)
/Video_bus/MCU_pixelData.D_{15}: IC5#2.37 (B_{2}_4), IC25#2.37 (B_{2}_4)
/Video_bus/MCU_pixelData.D_{16}: IC5#2.36 (B_{2}_5), IC25#2.36 (B_{2}_5)
/Video_bus/MCU_pixelData.D_{17}: IC5#2.35 (B_{2}_6), IC25#2.35 (B_{2}_6)
/Video_bus/MCU_pixelData.D_{18}: IC5#2.34 (B_{2}_7), IC25#2.34 (B_{2}_7)
/Video_bus/MCU_pixelData.D_{19}: IC5#2.33 (B_{2}_8), IC25#2.33 (B_{2}_8)
/Video_bus/MCU_pixelData.D_{20}: IC5#2.32 (B_{2}_9), IC25#2.32 (B_{2}_9)
/Video_bus/MCU_pixelData.D_{21}: IC5#2.31 (B_{2}_10), IC25#2.31 (B_{2}_10)
/Video_bus/MCU_pixelData.D_{22}: IC5#2.30 (B_{2}_11), IC25#2.30 (B_{2}_11)
/Video_bus/MCU_pixelData.D_{23}: IC5#2.29 (B_{2}_12), IC25#2.29 (B_{2}_12)
GND: C1.1, C4.1, C5.2, C6.2, C7.2, C12.2, C13.2, C14.2, C15.2, C16.2, C17.2, C18.2, C19.2, C20.2, C21.2, C22.2, C23.2, C24.2, C25.2, C26.2, IC1.6 (GND), IC2.8 (GND_1), IC2.19 (GND_2), IC2.38 (GND_3), IC2.49 (GND_4), IC3.8 (GND), IC4.8 (GND), IC5.8 (GND_1), IC5.19 (GND_2), IC5.25 (A_{2}_9), IC5.26 (A_{2}_10), IC5.27 (A_{2}_11), IC5.28 (A_{2}_12), IC5.29 (B_{2}_12), IC5.30 (B_{2}_11), IC5.31 (B_{2}_10), IC5.32 (B_{2}_9), IC5.38 (GND_3), IC5.49 (GND_4), IC5#2.8 (GND_1), IC5#2.19 (GND_2), IC5#2.38 (GND_3), IC5#2.49 (GND_4), IC6.8 (GND), IC7.8 (GND), IC8.7 (GND), IC9.7 (GND), IC10.7 (GND), IC11.8 (GND), IC12.8 (GND), IC13.8 (GND), IC14.8 (GND), IC15.7 (GND), IC16.7 (GND), IC17.7 (GND), IC18.7 (GND), IC19.7 (GND), IC20.7 (GND), IC21.8 (GND), IC21.11 (J), IC21.12 (K), IC21.13 (~CLK), IC21.15 (~CLR), IC22.8 (GND_1), IC22.19 (GND_2), IC22.29 (B_{2}_12), IC22.30 (B_{2}_11), IC22.31 (B_{2}_10), IC22.32 (B_{2}_9), IC22.38 (GND_3), IC22.49 (GND_4), IC22#2.8 (GND_1), IC22#2.19 (GND_2), IC22#2.38 (GND_3), IC22#2.49 (GND_4), IC23.7 (GND), IC24.8 (GND_1), IC24.19 (GND_2), IC24.25 (A_{2}_9), IC24.26 (A_{2}_10), IC24.27 (A_{2}_11), IC24.28 (A_{2}_12), IC24.29 (B_{2}_12), IC24.30 (B_{2}_11), IC24.31 (B_{2}_10), IC24.32 (B_{2}_9), IC24.38 (GND_3), IC24.49 (GND_4), IC24#2.8 (GND_1), IC24#2.19 (GND_2), IC24#2.29 (B_{2}_12), IC24#2.30 (B_{2}_11), IC24#2.31 (B_{2}_10), IC24#2.32 (B_{2}_9), IC24#2.38 (GND_3), IC24#2.49 (GND_4), IC25.8 (GND_1), IC25.19 (GND_2), IC25.38 (GND_3), IC25.49 (GND_4), IC25#2.8 (GND_1), IC25#2.19 (GND_2), IC25#2.38 (GND_3), IC25#2.49 (GND_4), IC26.8 (GND_1), IC26.19 (GND_2), IC26#2.8 (GND_1), IC26#2.19 (GND_2), IC26#2.25 (A_{2}_9), IC26#2.26 (A_{2}_10), IC26#2.27 (A_{2}_11), IC26#2.28 (A_{2}_12), IC26#2.29 (B_{2}_12), IC26#2.30 (B_{2}_11), IC26#2.31 (B_{2}_10), IC26#2.32 (B_{2}_9), IC26#2.38 (GND_3), IC26#2.49 (GND_4), IC27.2 (Dir_(AB|~BA)), IC27.11 (GND), IC27.12 (GND), IC27.13 (GND), IC27.22 (~OE), IC28.8 (GND_1), IC28.19 (GND_2), IC28.38 (GND_3), IC28.49 (GND_4), IC28#2.8 (GND_1), IC28#2.19 (GND_2), IC28#2.29 (B_{2}_12), IC28#2.30 (B_{2}_11), IC28#2.31 (B_{2}_10), IC28#2.32 (B_{2}_9), IC28#2.38 (GND_3), IC28#2.49 (GND_4), IC29.8 (GND_1), IC29.19 (GND_2), IC29.25 (A_{2}_9), IC29.26 (A_{2}_10), IC29.27 (A_{2}_11), IC29.28 (A_{2}_12), IC29.29 (B_{2}_12), IC29.30 (B_{2}_11), IC29.31 (B_{2}_10), IC29.32 (B_{2}_9), IC29.38 (GND_3), IC29.49 (GND_4), IC29#2.8 (GND_1), IC29#2.19 (GND_2), IC29#2.29 (B_{2}_12), IC29#2.30 (B_{2}_11), IC29#2.31 (B_{2}_10), IC29#2.32 (B_{2}_9), IC29#2.38 (GND_3), IC29#2.49 (GND_4), IC30.9 (BCB1), IC30.10 (BCB0), IC30.21 (RCR8), IC30.22 (RCR9), IC30.27 (GY9), IC30.28 (GY8), J1.1, U6.8 (~CE), U6.12 (GND), U6.34 (GND), U6.37 (~OE), U7.8 (~CE), U7.12 (GND), U7.34 (GND), U7.37 (~OE), U8.8 (~CE), U8.12 (GND), U8.34 (GND), U8.37 (~OE), U9.8 (~CE), U9.12 (GND), U9.34 (GND), U9.37 (~OE), U10.8 (~CE), U10.12 (GND), U10.34 (GND), U10.37 (~OE), U11.8 (~CE), U11.12 (GND), U11.34 (GND), U11.37 (~OE)
unnamed: C2.1, C3.1, U1.71 (VCAP), U1.106 (VCAP)
unnamed: C2.2, C3.2
unnamed: IC6.10 (~CLK), IC8.6 (&)
unnamed: IC7.10 (~CLK), IC8.8 (&)
unnamed: IC10.6 (&), IC11.3 (J)
unnamed: IC10.8 (&), IC11.11 (J)
unnamed: IC10.10 (B), IC11.5 (Q), IC17.4 (C)
unnamed: IC11.9 (Q), IC15.1 (A), IC17.12 (C)
unnamed: IC11.7 (~Q), IC17.5 (D)
unnamed: IC12.3 (J), IC15.6 (&)
unnamed: IC12.5 (Q), IC16.2 (B), IC16.12 (C)
unnamed: IC12.6 (~Q), IC17.13 (D)
unnamed: IC12.11 (J), IC16.6 (&)
unnamed: IC12.7 (~Q), IC16.13 (D)
unnamed: IC9.8 (&), IC13.3 (J)
unnamed: IC13.5 (Q), IC18.4 (C), IC18.12 (C)
unnamed: IC13.11 (J), IC18.6 (&)
unnamed: IC13.9 (Q), IC19.2 (B), IC19.12 (C)
unnamed: IC13.7 (~Q), IC18.13 (D)
unnamed: IC14.3 (J), IC19.6 (&)
unnamed: IC14.5 (Q), IC20.1 (A), IC20.12 (C)
unnamed: IC14.6 (~Q), IC19.13 (D)
unnamed: IC14.11 (J), IC20.6 (&)
unnamed: IC14.7 (~Q), IC20.13 (D)
unnamed: IC21.1 (~CLK), IC23.6 (&)
unnamed: IC22#2.56 (1~OE), IC24.56 (1~OE)
unnamed: IC22#2.55 (2~OE), IC24.55 (2~OE)
unnamed: IC25.56 (1~OE), IC26#2.56 (1~OE)
unnamed: IC25.55 (2~OE), IC26#2.55 (2~OE)
unnamed: IC26.38 (GND_3), IC26.49 (GND_4)
unnamed: IC28.56 (1~OE), IC29.56 (1~OE)
unnamed: IC28.55 (2~OE), IC29.55 (2~OE)
unnamed: U1.16 (VSS), U1.38 (VSS), U1.51 (VSS), U1.61 (VSS), U1.83 (VSS), U1.94 (VSS), U1.107 (VSS), U1.120 (VSS), U1.130 (VSS)
unnamed: U2.23 (VSS), U2.35 (VSS), U2.47 (VSS)
unnamed: U3.A1 (VSS), U3.A19 (VSS), U3.B2 (VSS), U3.B6 (VSS), U3.C3 (VSS), U3.C12 (VSS), U3.C13 (VSS), U3.C14 (VSS), U3.C15 (VSS), U3.C16 (VSS), U3.C17 (VSS), U3.D1 (VSS), U3.D4 (VSS), U3.D5 (VSS), U3.D8 (VSS), U3.E2 (VSS), U3.E4 (VSS), U3.E5 (VSS), U3.E6 (VSS), U3.E8 (VSS), U3.E10 (VSS), U3.E12 (VSS), U3.E14 (VSS), U3.E16 (VSS), U3.F5 (VSS), U3.F7 (VSS), U3.F9 (VSS), U3.F11 (VSS), U3.F15 (VSS), U3.G2 (VSS), U3.G4 (VSS), U3.G6 (VSS), U3.G8 (VSS), U3.G10 (VSS), U3.G12 (VSS), U3.G14 (VSS), U3.H5 (VSS), U3.H7 (VSS), U3.H9 (VSS), U3.H11 (VSS), U3.H13 (VSS), U3.H15 (VSS), U3.J3 (VSS), U3.J6 (VSS), U3.J8 (VSS), U3.J10 (VSS), U3.J12 (VSS), U3.J14 (VSS), U3.K2 (VSS), U3.K5 (VSS), U3.K7 (VSS), U3.K9 (VSS), U3.K11 (VSS), U3.K13 (VSS), U3.K15 (VSS), U3.L6 (VSS), U3.L8 (VSS), U3.L10 (VSS), U3.L12 (VSS), U3.L14 (VSS), U3.M5 (VSS), U3.M7 (VSS), U3.M9 (VSS), U3.M11 (VSS), U3.M13 (VSS), U3.M15 (VSS), U3.N6 (VSS), U3.N8 (VSS), U3.N10 (VSS), U3.N12 (VSS), U3.N14 (VSS), U3.P7 (VSS), U3.P9 (VSS), U3.P11 (VSS), U3.P13 (VSS), U3.P15 (VSS), U3.R2 (VSS), U3.R6 (VSS), U3.R8 (VSS), U3.R10 (VSS), U3.R12 (VSS), U3.R14 (VSS), U3.R16 (VSS), U3.T4 (VSS), U3.U3 (VSS), U3.U6 (VSS), U3.U8 (VSS), U3.U17 (VSS), U3.W1 (VSS), U3.W19 (VSS)
unnamed: U3.N4 (VSSA), U3.P5 (VSSA), U3.R5 (VSSA)
unnamed: U3.U13 (VSS_USBHS), U3.U14 (VSS_USBHS), U3.V12 (VSS_USBHS), U3.V15 (VSS_USBHS)
VCC_AUX_3V3: C1.2, J1.8
VCC_VGA_3V3: IC6.16 (VCC), IC7.16 (VCC)
VCC_VGA_5V: C4.2, C5.1, C6.1, C7.1, C12.1, C13.1, C14.1, C15.1, C16.1, C17.1, C18.1, C19.1, C20.1, C21.1, C22.1, C23.1, C24.1, C25.1, C26.1, IC1.7 (VDD), IC1.8 (OE), IC2.17 (VCC), IC3.16 (VCC), IC4.16 (VCC), IC5.17 (VCC), IC5#2.17 (VCC), IC8.1 (A), IC8.9 (A), IC8.14 (VCC), IC9.14 (VCC), IC10.1 (A), IC10.9 (A), IC10.14 (VCC), IC11.4 (~PRESET), IC11.10 (~PRESET), IC11.16 (VCC), IC12.4 (~PRESET), IC12.10 (~PRESET), IC12.16 (VCC), IC13.4 (~PRESET), IC13.10 (~PRESET), IC13.16 (VCC), IC14.4 (~PRESET), IC14.10 (~PRESET), IC14.16 (VCC), IC15.14 (VCC), IC16.1 (A), IC16.9 (A), IC16.10 (B), IC16.14 (VCC), IC17.1 (A), IC17.2 (B), IC17.9 (A), IC17.10 (B), IC17.14 (VCC), IC18.1 (A), IC18.2 (B), IC18.9 (A), IC18.10 (B), IC18.14 (VCC), IC19.1 (A), IC19.9 (A), IC19.10 (B), IC19.14 (VCC), IC20.9 (A), IC20.10 (B), IC20.14 (VCC), IC21.2 (K), IC21.3 (J), IC21.10 (~PRESET), IC21.14 (~CLR), IC21.16 (VCC), IC22.17 (VCC), IC22.33 (B_{2}_8), IC22#2.17 (VCC), IC23.14 (VCC), IC24.17 (VCC), IC24#2.17 (VCC), IC25.17 (VCC), IC25#2.17 (VCC), IC26.17 (VCC), IC26#2.17 (VCC), IC27.1 (VCCA), IC28.17 (VCC), IC28#2.17 (VCC), IC29.17 (VCC), IC29#2.17 (VCC), IC29#2.33 (B_{2}_8), U6.11 (VDD), U6.33 (VDD), U7.11 (VDD), U7.33 (VDD), U8.11 (VDD), U8.33 (VDD), U9.11 (VDD), U9.33 (VDD), U10.11 (VDD), U10.33 (VDD), U11.11 (VDD), U11.33 (VDD)
~FrontBufferBackBuffer: IC2.55 (2~OE), IC2.56 (1~OE), IC21.6 (~Q), IC22.55 (2~OE), IC22.56 (1~OE), IC25#2.55 (2~OE), IC25#2.56 (1~OE), IC28#2.55 (2~OE), IC28#2.56 (1~OE)

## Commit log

2026-03-14 Initial commit.
